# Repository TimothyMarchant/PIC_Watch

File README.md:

# PIC_Watch
A digital watch that tells the time and temperature.  It uses the PIC16F15225 microcontroller.  The screen is a 0.96 inch OLED (SSD1306).  
The purpose of this project was to make an actual embedded application because I was in need of a watch.  

Here are some pictures from start to finish.  

Breadboard prototype

prototype PCB

Finalized PCB with components soldered on
Without the screen (this is actually a different PCB than the other two pictures!)

Back side

With the screen

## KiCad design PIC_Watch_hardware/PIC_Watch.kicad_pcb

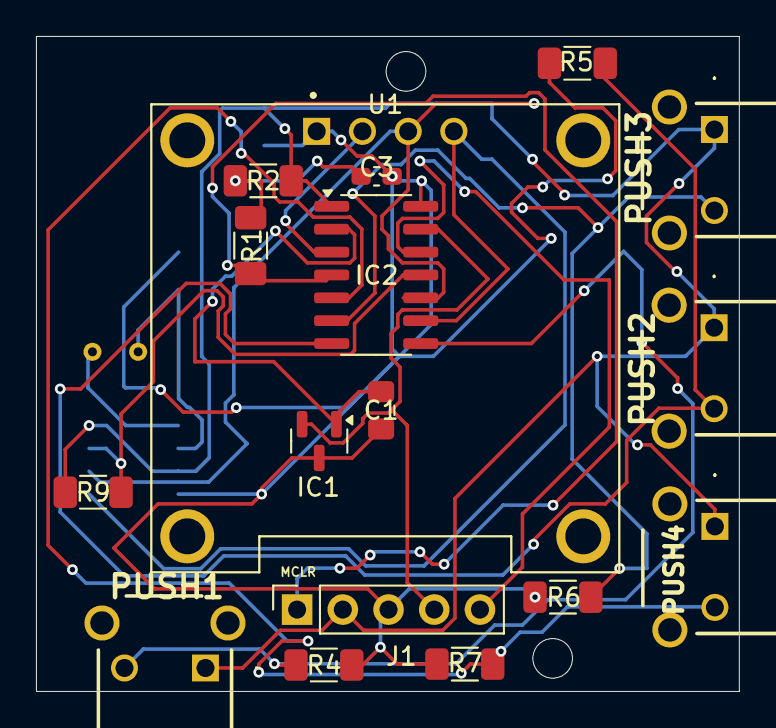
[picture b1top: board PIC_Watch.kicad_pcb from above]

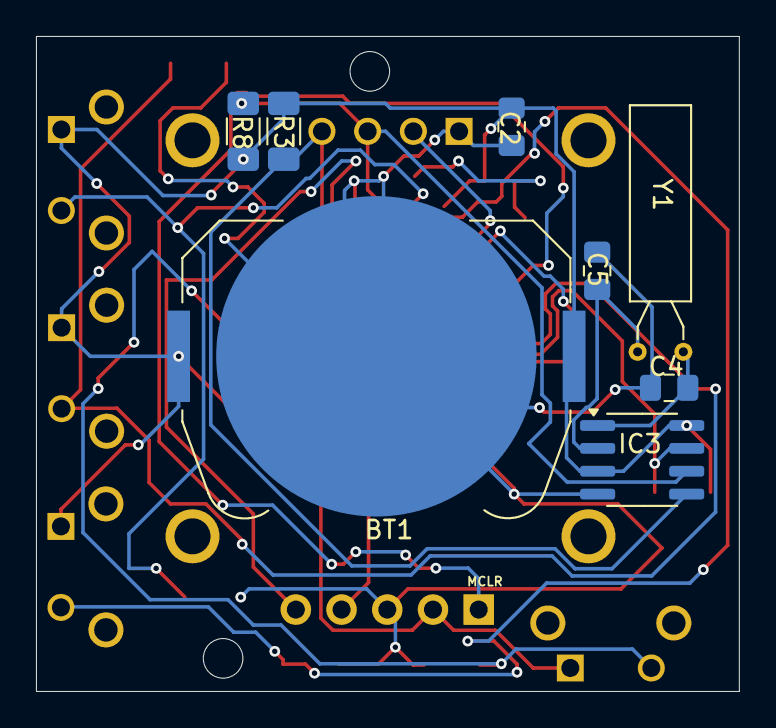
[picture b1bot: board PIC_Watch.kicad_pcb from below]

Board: 2 copper layers, 39.1 x 36.4 mm, 25 parts (8 on the bottom side), 17 nets.

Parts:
BT1: Battery_Cell; BatteryHolder_Keystone_3034_1x20mm
C1, C2: 0.1uF; C_0805_2012Metric_Pad1.18x1.45mm_HandSolder
C3: 0.01uF; C_0603_1608Metric_Pad1.08x0.95mm_HandSolder
C4, C5: 6pF; C_0805_2012Metric_Pad1.18x1.45mm_HandSolder
IC1: MCP9700AT-E_TT; SOT-23
IC2: PIC16F15225-I_SL; SOIC-14_3.9x8.7mm_P1.27mm
IC3: MCP7940NT-I_SN; SOIC-8_3.9x4.9mm_P1.27mm
J1: Conn_01x05_Pin; PinSocket_1x05_P2.54mm_Vertical
PUSH1, PUSH2, PUSH3, PUSH4: TS11674153BK160RAD
R1: 470 ohms; R_1206_3216Metric_Pad1.30x1.75mm_HandSolder
R2, R4, R5, R6, R7, R9: 10k ohms; R_1206_3216Metric_Pad1.30x1.75mm_HandSolder
R3, R8: 4.7k ohms; R_1206_3216Metric_Pad1.30x1.75mm_HandSolder
U1: DM-OLED096-636; MODULE_DM-OLED096-636
Y1: Crystal; Crystal_AT310_D3.0mm_L10.0mm_Horizontal

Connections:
+3V0: BT1.1 (+), C2.1, IC2.1 (VDD), IC3.3 (VBAT), IC3.8 (VCC), J1.2, PUSH1.1, PUSH2.1, PUSH3.1, PUSH4.1, R2.1, R3.2, R8.2, R9.2
GND: BT1.2 (-), C1.1, C2.2, C3.2, C4.2, C5.1, IC1.3 (GND), IC2.14 (VSS), IC3.4 (VSS), J1.3, R4.1, R5.1, R6.1, R7.1, U1.1 (GND)
unnamed: C3.1, R1.1, R2.2
unnamed: C1.2, IC1.1 (VDD), IC2.2 (RA5)
unnamed: IC1.2 (VOUT), IC2.13 (RA0/ICSPDAT), J1.4
unnamed: IC2.12 (RA1/ICSPCLK), J1.5
unnamed: IC2.11 (RA2), IC3.7 (MFP), R9.1
unnamed: IC2.3 (RA4), U1.2 (VCC_IN)
unnamed: IC2.10 (RC0), IC3.6 (SCL), R8.1, U1.3 (SCL)
unnamed: IC2.9 (RC1), IC3.5 (SDA), R3.1, U1.4 (SDA)
unnamed: IC2.8 (RC2), PUSH1.2, R4.2
unnamed: IC2.7 (RC3), PUSH2.2, R5.2
unnamed: IC2.6 (RC4), PUSH3.2, R6.2
unnamed: IC2.5 (RC5), PUSH4.2, R7.2
unnamed: IC2.4 (~MCLR/VPP/RA3), J1.1, R1.2
unnamed: C4.1, IC3.1 (X1), Y1.1
unnamed: C5.2, IC3.2 (X2), Y1.2

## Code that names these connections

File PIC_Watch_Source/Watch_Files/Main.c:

#include "CONFIG.h"
#include "I2C_Drivers_PIC16F15225.h"
#include "SSD1306_Drivers.h"
#include "MCP9700_Drivers.h"
#include "MCP7940_Drivers.h"
/* This project uses the MCP7940N RTC, SSD1306, and the MCP9700 analog temperature sensor
 * This microcontroller was picked for several reasons
 * 1st, I had these in my house already and seemed to be big enough to do the job.
 * 2nd it's small enough for a <1.5 inch PCB (need it to be smaller than this more than likely; the PCB that is).
 * 
 */
#ifndef _XTAL_FREQ
#define _XTAL_FREQ 32000000
#endif
#define Button1 PORTCbits.RC2
#define Button2 PORTCbits.RC3
#define Button3 PORTCbits.RC4
#define Button4 PORTCbits.RC5
#define INTDATA 0xFF
#define PORTCButtons 0b00111100
#define OLED_POWER LATA4
void SendNumber(unsigned int);
void SendByte(unsigned char);
void HandleButton(unsigned char);
void EnableInterrupts(void);
void IncrementTimer1cnt(void);
unsigned char GetTimer1cnt(void);
unsigned int timer0cnt = 0;
unsigned char data = 0;
_Bool DeepSleep = 0;
_Bool IsPressed = 0;
_Bool NeedToUpdateTime=0;
void GotoSleep(void);
void DisplayTime(void);
void DisplayState(void);
void UpdateTimeArray(void);
void UpdateDateArray(void);
void UpdateYearArray(void);
void __interrupt() ISR(void) {
    //I2C recovery
    if (TMR1IF) {
        TMR1ON=0;
        IncrementTimer1cnt();
        TMR1IF=0;
        //timeout has clearly gone on too long restart the device after sending 9 clock pulses.
        if (GetTimer1cnt()==0xFF){
            ForceReset();
        }
        TMR1=0;
        TMR1ON=1;
    }
    //wakeup device.
    if (IOCCF>0) {
        //for debouncing
        __delay_ms(50);
        //get inputs from RC2-RC5 only.
        data = (PORTC & PORTCButtons)>>2;
        IOCCF = 0;
        IOCIF = 0;
        NeedToUpdateTime=0;
    }
    //alarm interrupt
    if (IOCAF>0){
        NeedToUpdateTime=1;
        //we need not update anything here, as the alarm pin will not change states until we modify the internal registers of the RTC.
        //The compiler gave a warning when we call such methods saying possible stack overflow.
        IOCIF=0;
        IOCAF=0;
    }
}
//this is for other files so that it can be changed elsewhere.
void GotoSleep(void){
    //
    DeepSleep=1;
    //do some other things.
}
void main(void) {
    TRISA = 0x00;
    LATA = 0x00;
    TRISA0=1;
    ANSELA=0x01;
    TRISA2=1;
    LATC = 0x00;
    //RC2-RC5 are all inputs.
    TRISC = 0xFF;
    ANSELC = 0x00;
    WPUC = 0x00;
    WPUA=0x00;
    OLED_POWER=1;
    Temp_Init(&LATA, 5);
    EnableInterrupts();
    I2C_Init();
    __delay_ms(50);
    init_OLED();
    MCP7940_Init();
    while (1) {
        //don't turn off the screen immediately wait some time then turn it off.
        HandleButton(data);
        if (DeepSleep) {
            DisplayTurnOff();
            //turn off alarm0 no interrupts are made in deep sleep.
            TurnOffInterrupt();
            //wait a little before just turning off the screen.
            __delay_ms(1);
            ClearAlarm0Interrupt();
            OLED_POWER=0;
            TMR1IE=0;
            data=0x00;
        }
        SLEEP();
        //We need this here instead of the ISR to avoid stack overflow.  The stack can only go 15 deep according to the datasheet (the compiler made a warning about it).
        
        //turn the screen back on.
        if (DeepSleep&&data!=0x00) {
            OLED_POWER=1;
            //wait some time before sending any commands.  the datasheet of the SSD1306 has the timing diagrams lasting a few microseconds, but I rather just wait longer
            //to avoid any problems.
            __delay_ms(25);
            init_OLED();
            //prevents the screen from having garbage shown.
            DisplayTurnOff();
            DeepSleep = 0;
        }
        if (NeedToUpdateTime){
            //update alarm time.
            updatealarm0();
            data=INTDATA;
            DeepSleep=0;
            NeedToUpdateTime=0;
        }
    }
}

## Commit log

2024-08-03 Uploaded all code files
    This is a minimal operating product. Most functionality is finished, but I rather have this uploaded now.
2024-08-03 Update Clock_Screens.c
    Uncommented a line. This prints the temperature. This was commented out because the prototyped PCB I had I guess I screwed up something when soldering the temperature sensor on and it was causing a s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
2024-08-03 Update Required_Files_MCP7940.c
    Fixed a bug if it were a leap year the month would appear incorrectly (If left alone we would have 32 months which is clearly nonsensical.)
2024-08-05 added recovery method file
2024-08-05 Create Notes on I2C Recovery
2024-08-08 added more recovery files.
    Interrupt_Toggle will be updated as needed, it simply turns off all interrupts excluding timer 1.
2024-08-08 Update Required_I2C_Methods.c
    added timeout for I2C_Wait() and updated I2C_Stop() to fix a stuck bus that gets past I2C_Wait() (for some reason).
2024-08-08 added file for enabling interrupts at startup
2024-08-08 Update Main.c
    updated interrupt ISR to add support for I2C_Wait timeout.
    also rearranged a few things for startup.
2024-08-08 Update Notes on I2C Recovery
2024-08-08 Update Enable_Interrupts.c
    updated some comments on timer1.
2024-08-15 Update MCP7940_Drivers.h
    updated header with more methods
2024-08-16 Update Main.c
    Added IO pin to control SSD1306 power supply. Limited testing has shown no problems.
2024-08-18 Update Main.c
    Minor cleanup of unnecessary code that did nothing.
2024-08-18 Update Clock_Screens.c
    Modified positioning of some things on the screen. Also added a check for February 29th. And made sure to clear the MCP7900 interrupt flag when in the settings to prevent it from being set where it i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
2024-08-18 Update Screen_Logic.c
    Added handling for incorrect dates, so the user can't set it to dates like 00/39 or 12/00 (and other weird times). Also cleaned up unnecessary code and added some more comments. From all testing this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
2024-08-18 Added schematic
    This new folder will hold the PCB files soon enough. And any other CAD/model files.
2024-08-25 Rename output.pdf to Schematic.pdf
2024-08-25 Added Kicad PCB design
    These are not the gerber files.
2024-08-25 Create Battery Life notes
    These are the notes on power consumption.
2024-08-25 Create OLED library notes
2024-08-25 Update Battery Life notes
    updated notes to be more realistic to actual use case
2024-08-27 Added pdf of the PCB
2024-08-28 Rename PIC_Watch_PCB to PIC_Watch_PCB.pdf
2024-09-12 Create PCB_Notes_IMPORTANT
2024-09-12 Update Main.c fixes major problem
    As it turns out I forgot to reinitialize the screen after power off, so when I finally got the PCBs and soldered the PIC onto it and was testing it, I kept running into problems with the device reset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
2024-10-02 Update Battery Life notes
2024-10-13 Update Battery Life notes
    Updated notes on further testing
2025-03-07 Update README.md
    fixed typo in readme
